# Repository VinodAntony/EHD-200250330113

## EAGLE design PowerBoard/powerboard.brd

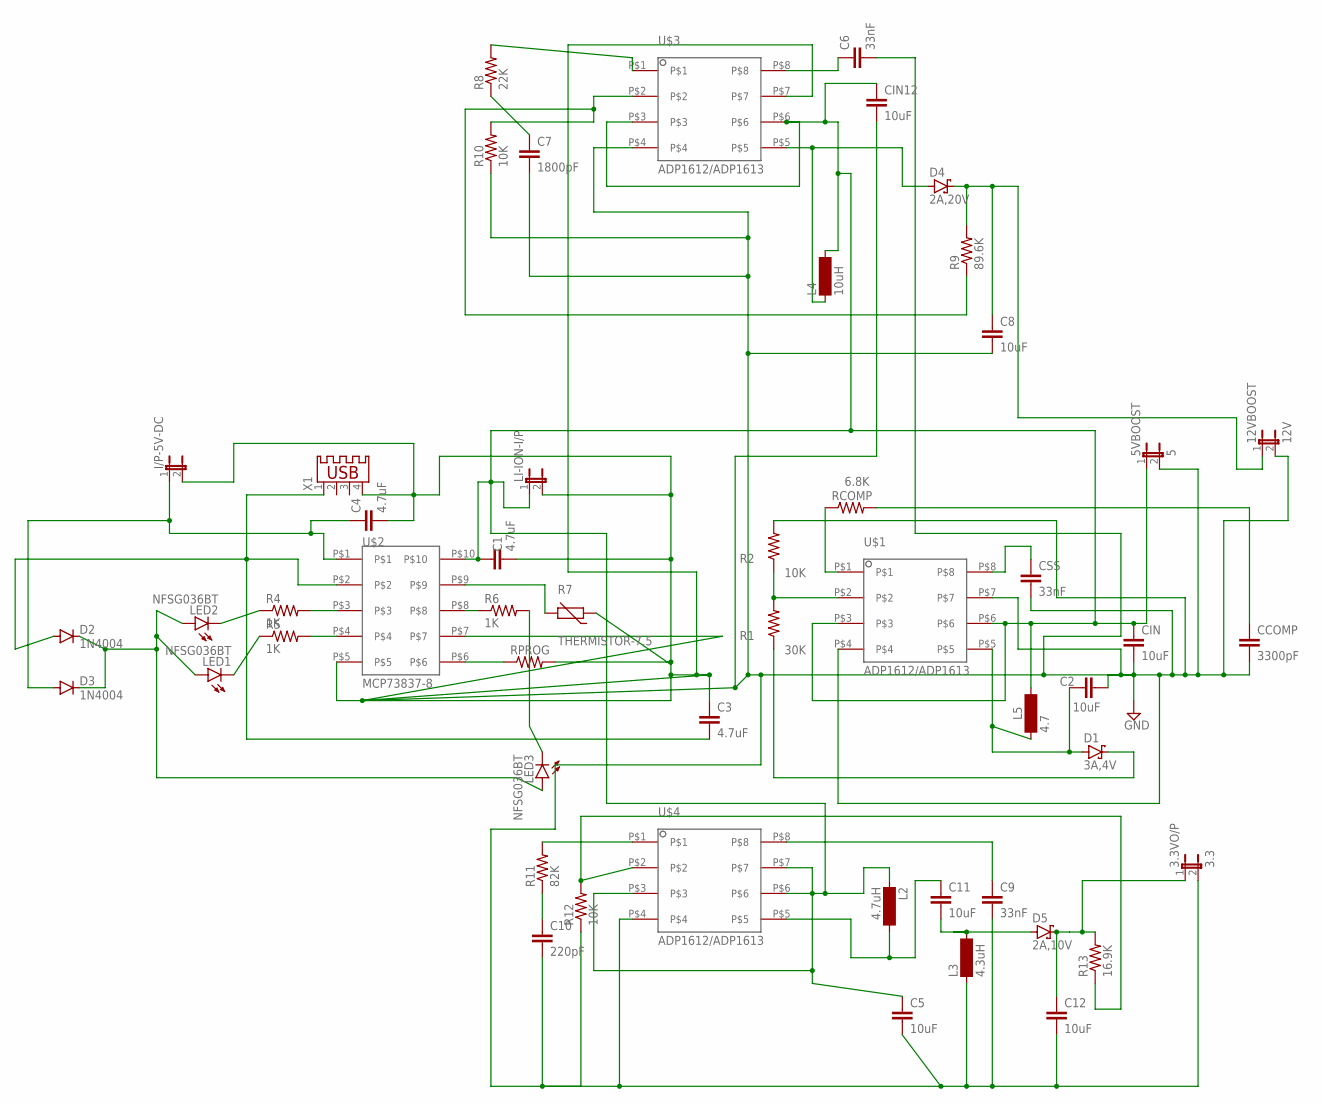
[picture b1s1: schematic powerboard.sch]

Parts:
3.3VO/P: 3.3; JP1
5VBOOST: 5; JP1
12VBOOST: 12V; JP1
C1, C3, C4: 4.7uF; C2.5-3
C2, C5, C11, C12: 10uF; C2.5-2
C6: 33nF; C2.5-3
C7: 1800pF; C2.5-3
C8: 10uF; C2.5-3
C9: 33nF; C2.5-2
C10: 220pF; C2.5-2
CCOMP: 3300pF; C2.5-2
CIN, CIN12: 10uF; C2.5-3
CSS: 33nF; C2.5-2
D1: 3A,4V; DO35-7
D2, D3: 1N4004; DO41-10
D4: 2A,20V; DO35-7
D5: 2A,10V; DO35-7
I/P-5V-DC: JP1E; JP1
L2: 4.7uH; BS75
L3: 4.3uH; BS75
L4: 10uH; BS75
L5: 4.7; BS75
LED1, LED2, LED3: NFSG036BT
LI-ION-I/P: JP1E; JP1
R1: 30K; 0207/10
R2: 10K; 0207/10
R4, R5, R6: 1K; R0805
R7: THERMISTOR-7,5; R-7,5
R8: 22K; 0204/7
R9: 89.6K; 0204/7
R10, R12: 10K; 0204/7
R11: 82K; 0204/7
R13: 16.9K; 0204/7
RCOMP: 6.8K; 0207/10
RPROG: R-US_R0805; R0805
U$1, U$3, U$4: ADP1612/ADP1613
U$2: MCP73837-8; MCP73837/8
X1: USB-A003

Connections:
unnamed: C6.1, U$3.P$8
unnamed: C2.1, D1.A, L5.1, U$1.P$5
unnamed: R1.2, R2.1, U$1.P$2
unnamed: D1.C, R1.1
unnamed: RCOMP.1, U$1.P$1
unnamed: CCOMP.1, RCOMP.2
unnamed: CSS.1, U$1.P$8
unnamed: R7.2, U$2.P$9
unnamed: RPROG.1, U$2.P$6
unnamed: 5VBOOST.1, C1.1, C5.1, CIN.1, CIN12.1, L2.1, L4.2, L5.2, LI-ION-I/P.1, U$1.P$3, U$1.P$6, U$2.P$10, U$3.P$3, U$3.P$6, U$4.P$3, U$4.P$6, U$4.P$7
unnamed: R4.2, U$2.P$3
unnamed: R5.2, U$2.P$4
unnamed: R6.1, U$2.P$8
unnamed: LED2.C, R4.1
unnamed: LED1.C, R5.1
unnamed: LED3.C, R6.2
unnamed: D2.C, D3.C, LED1.A, LED2.A, LED3.A
unnamed: D4.A, L4.1, U$3.P$5
unnamed: C3.2, D2.A, U$2.P$2, X1.1
unnamed: R8.2, U$3.P$1
unnamed: C4.1, D3.A, I/P-5V-DC.1, U$2.P$1
unnamed: C7.1, R8.1
unnamed: R9.1, R10.2, U$3.P$2
unnamed: 12VBOOST.1, C8.1, D4.C, R9.2
unnamed: C11.1, L2.2, U$4.P$5
unnamed: C9.1, U$4.P$8
unnamed: 3.3VO/P.2, 5VBOOST.2, 12VBOOST.2, C1.2, C2.2, C3.1, C4.2, C5.2, C6.2, C7.2, C8.2, C9.2, C10.2, C12.2, CCOMP.2, CIN.2, CIN12.2, CSS.2, I/P-5V-DC.2, L3.1, LI-ION-I/P.2, R2.2, R7.1, R10.1, R12.1, RPROG.2, U$1.P$4, U$1.P$7, U$2.P$5, U$2.P$7, U$3.P$4, U$3.P$7, U$4.P$4, X1.4
unnamed: R11.2, U$4.P$1
unnamed: C10.1, R11.1
unnamed: R12.2, R13.1, U$4.P$2
unnamed: C11.2, D5.A, L3.2
unnamed: 3.3VO/P.1, C12.1, D5.C, R13.2

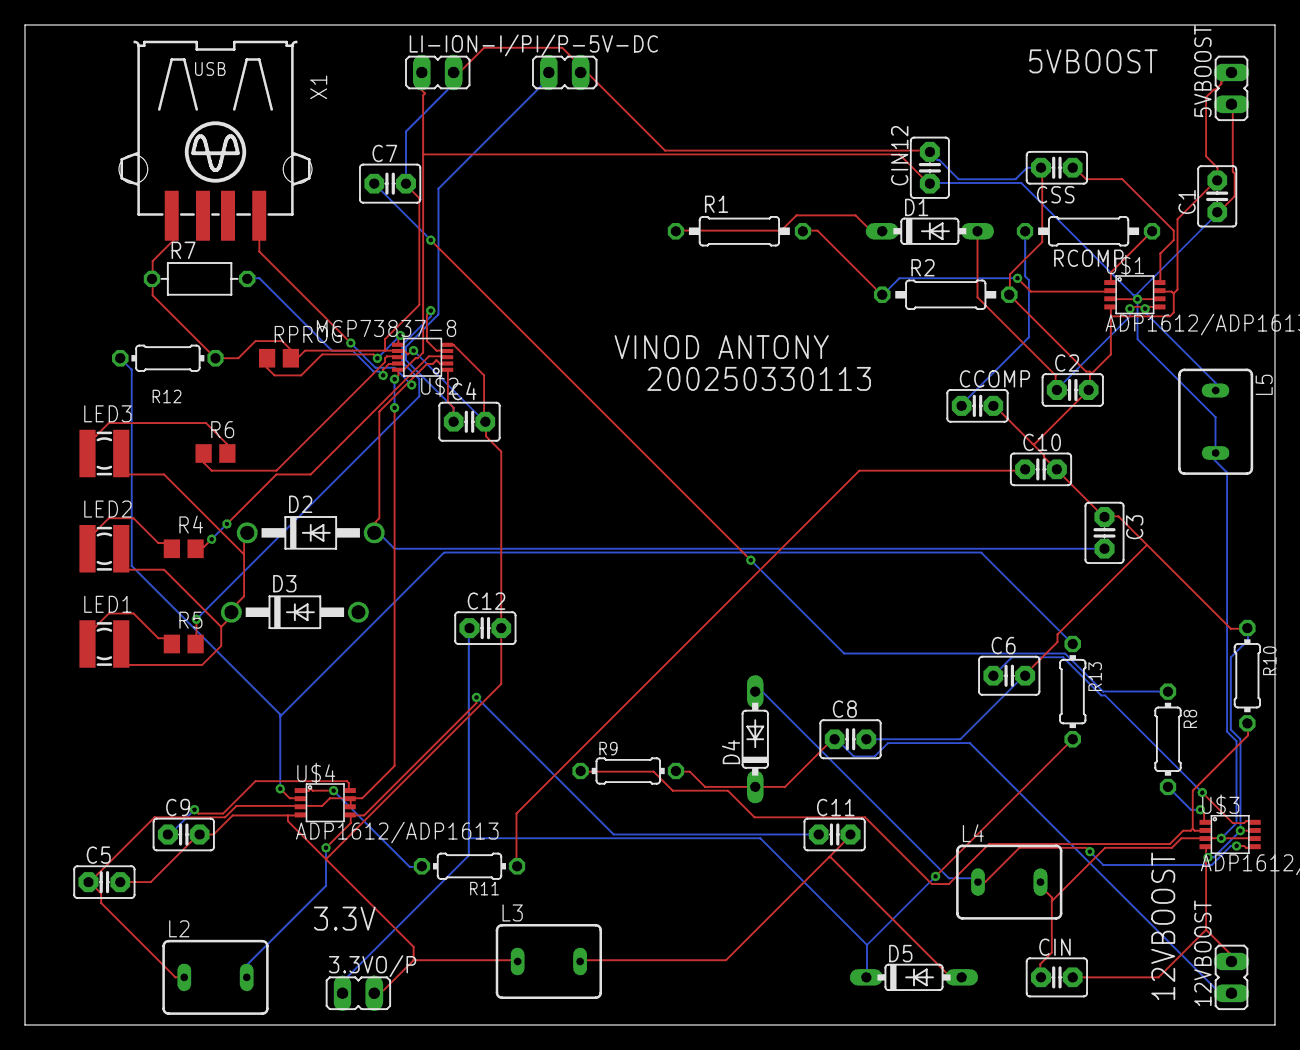
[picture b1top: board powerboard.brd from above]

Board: 2 copper layers, 100.0 x 80.0 mm, 52 parts (0 on the bottom side), 32 nets.

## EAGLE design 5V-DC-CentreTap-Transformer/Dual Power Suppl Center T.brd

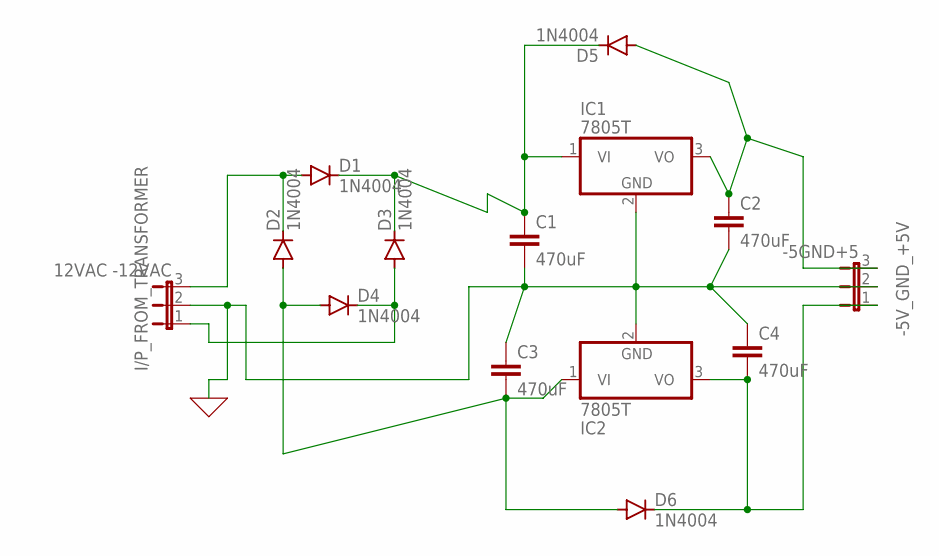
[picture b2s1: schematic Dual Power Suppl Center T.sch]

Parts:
-5V_GND_+5V: -5GND+5; JP2
C1, C2, C3, C4: 470uF; C2.5-3
D1, D2, D3, D4, D5, D6: 1N4004; DO41-10
I/P_FROM_TRANSFORMER: 12VAC -12VAC; JP2
IC1, IC2: 7805T; TO220H

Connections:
0: -5V_GND_+5V.2, C1.2, C2.2, C3.1, C4.1, I/P_FROM_TRANSFORMER.2, IC1.2 (GND), IC2.2 (GND)
unnamed: C3.2, D2.A, D4.A, D6.A, IC2.1 (VI)
unnamed: D1.A, D2.C, I/P_FROM_TRANSFORMER.3
unnamed: C1.1, D1.C, D3.C, D5.C, IC1.1 (VI)
unnamed: D3.A, D4.C, I/P_FROM_TRANSFORMER.1
unnamed: -5V_GND_+5V.3, C2.1, D5.A, IC1.3 (VO)
unnamed: -5V_GND_+5V.1, C4.2, D6.C, IC2.3 (VO)

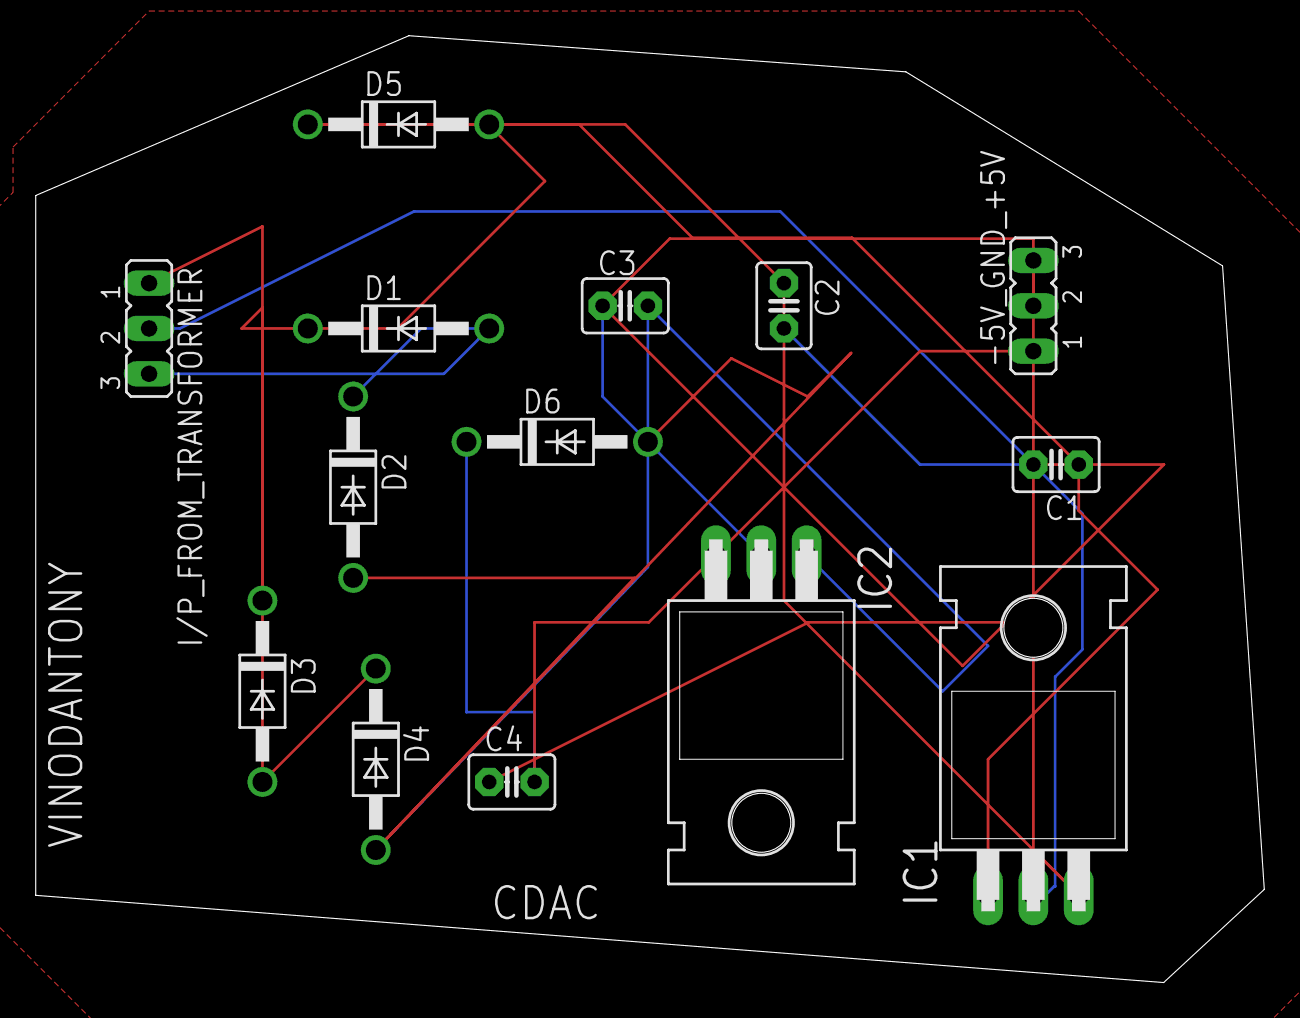
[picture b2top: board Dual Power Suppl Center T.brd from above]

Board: 2 copper layers, 68.8 x 53.0 mm, 14 parts (0 on the bottom side), 7 nets.

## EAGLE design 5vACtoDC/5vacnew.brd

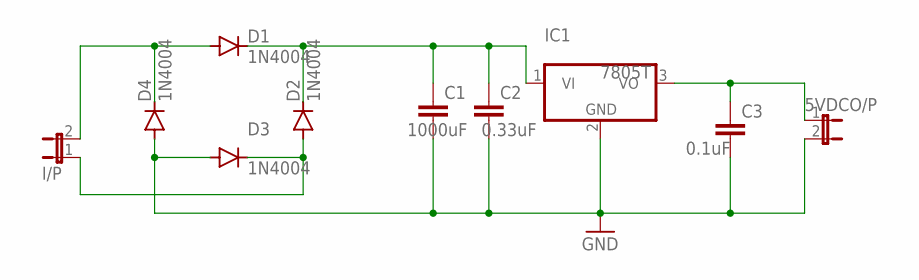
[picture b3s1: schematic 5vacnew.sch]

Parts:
5VDCO/P: JP1E; JP1
C1: 1000uF; C2.5-3
C2: 0.33uF; C2.5-3
C3: 0.1uF; C2.5-3
D1, D2, D3, D4: 1N4004; DO41-10
I/P: JP1E; JP1
IC1: 7805T; TO220H

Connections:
GND: 5VDCO/P.2, C1.2, C2.2, C3.2, D3.A, D4.A, IC1.2 (GND)
unnamed: D1.A, D4.C, I/P.2
unnamed: C1.1, C2.1, D1.C, D2.C, IC1.1 (VI)
unnamed: D2.A, D3.C, I/P.1
unnamed: 5VDCO/P.1, C3.1, IC1.3 (VO)

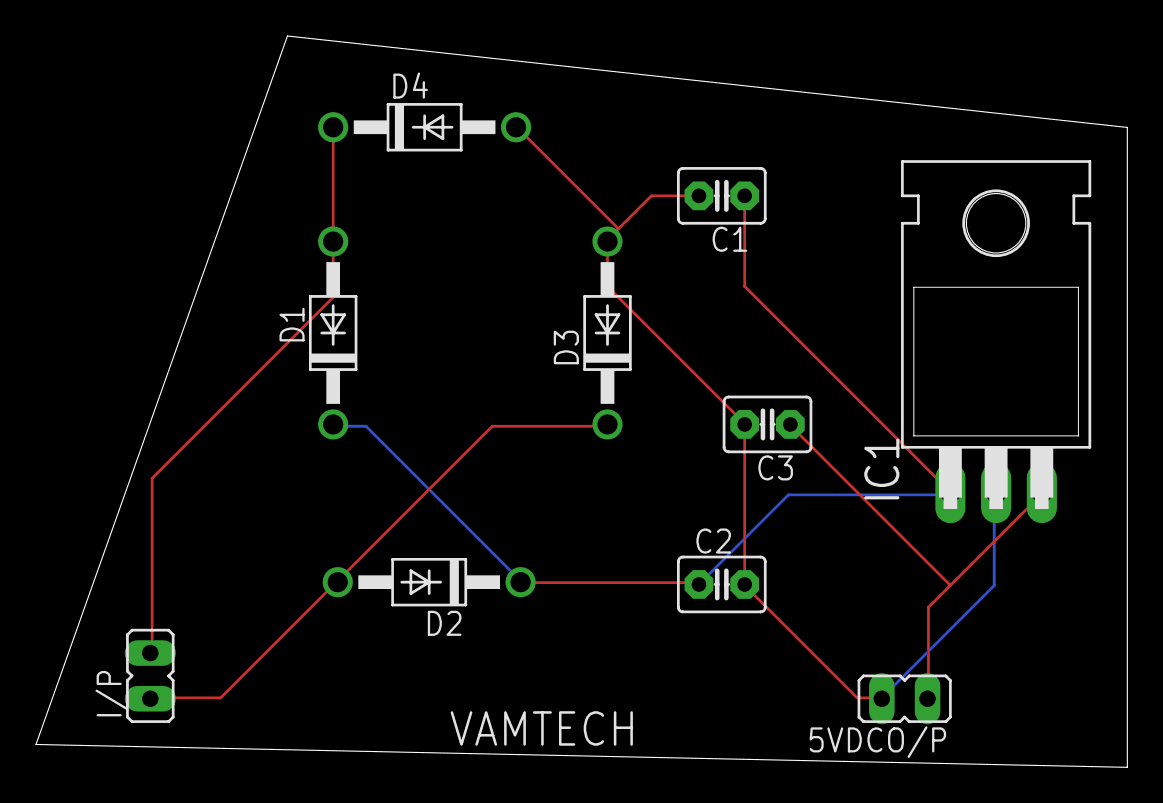
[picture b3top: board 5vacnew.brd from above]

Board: 2 copper layers, 60.6 x 40.6 mm, 10 parts (0 on the bottom side), 5 nets.

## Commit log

2020-09-29 Create 1
2020-09-30 Add files via upload
    Gerber Files
